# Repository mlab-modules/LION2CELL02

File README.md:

# LION2CELL02 - Dual-cell Li-Ion BMS with I2C interface and USB-C charging.

The LION2CELL02 module is designed to manage the charging and protection of the 2-cell Li-Ion battery stack. It incorporates advanced safe and efficient battery management features, utilizing the BQ40Z50-R2 fuel gauge and BQ25792 battery charger ICs.

## Features

The LION2CELL02 module include USB-C connector for quick charge connection. This allows for easy integration with USB-C power sources.

### BQ40Z50-R2 - Fuel Gauge

- Utilizes Impedance Track™ technology for accurate charge measurement.
- High-side protection N-FETs control.
- Integrated cell balancing during charging or at rest.
- Programmable protection features (voltage, current, temperature, charge timeout).
- JEITA, enhanced charging, and adaptive charging algorithms.
- Supports TURBO Mode 2.0 and Battery Trip Point (BTP).
- LED display for battery status.
- SMBus v1.1 interface for communication with the charger and host systems.

### BQ25792 Battery Charger

- Supports USB BC 1.2 charging standard.
- High-efficiency buck-boost charging for Li-Ion batteries.
- Programmable input current, charge current, and charge voltage.
- Integrated power path management.
- Protection features including overvoltage, undervoltage, overcurrent, and thermal protection.
- Low quiescent current for extended battery life.

## Power Delivery

The module supports BC 1.2 for charging. For the full USB Power Delivery (PD) support, an external USB PD controller is required. The MLAB [USBPDSINK01](https://www.mlab.cz/module/USBPDSINK01/) module can be used to enable PD functionality.

## Usage Instructions

1. Equip the LION2CELL02 module with pair of the suitable 16850 Li-Ion batteries.
2. Connect a USB-C power source to the module. For standard charging, ensure the power source complies with BC 1.2.
3. For USB PD, connect the USBPDSINK01 module to enable PD negotiation and charging.
4. Monitor the LED indicators for battery and charging status.
5. Connect to an MCU and use I2C/smbus for advanced features. 

## Safety and Protection

- The module includes multiple layers of protection for voltage, current, and temperature to ensure safe operation.
- Integrated cell balancing ensures equal charging across all cells, preventing overcharge and extending battery life.

## Applications

- UPS/battery backup systems
- Stand-alone measurement devices
- Scientific equipment

## Additional Resources

For further information, refer to the datasheets:
- [BQ40Z50-R2 Datasheet](https://www.ti.com/product/BQ40Z50-R2)
- [BQ25792 Datasheet](https://www.ti.com/product/BQ25792)

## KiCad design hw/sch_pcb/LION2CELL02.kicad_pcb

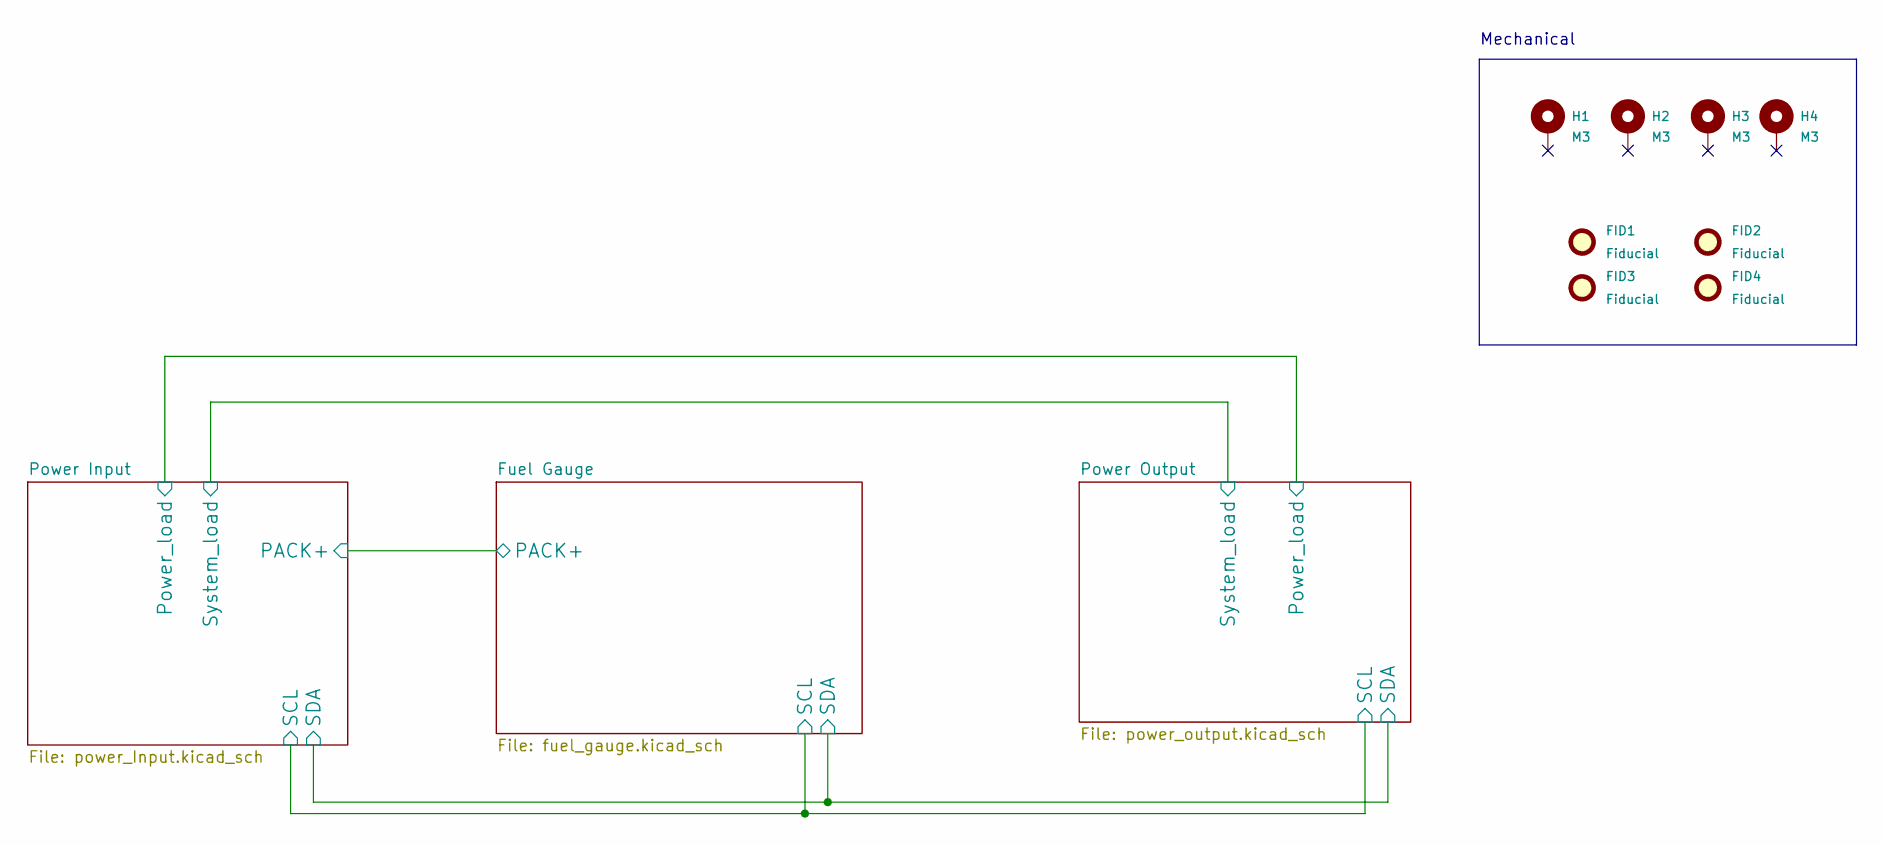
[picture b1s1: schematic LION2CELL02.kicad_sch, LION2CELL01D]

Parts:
FID1, FID2, FID3, FID4: Fiducial; Fiducial_1mm_Mask2mm
H1, H2, H3, H4: M3; MountingHole_3mm

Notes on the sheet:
Mechanical

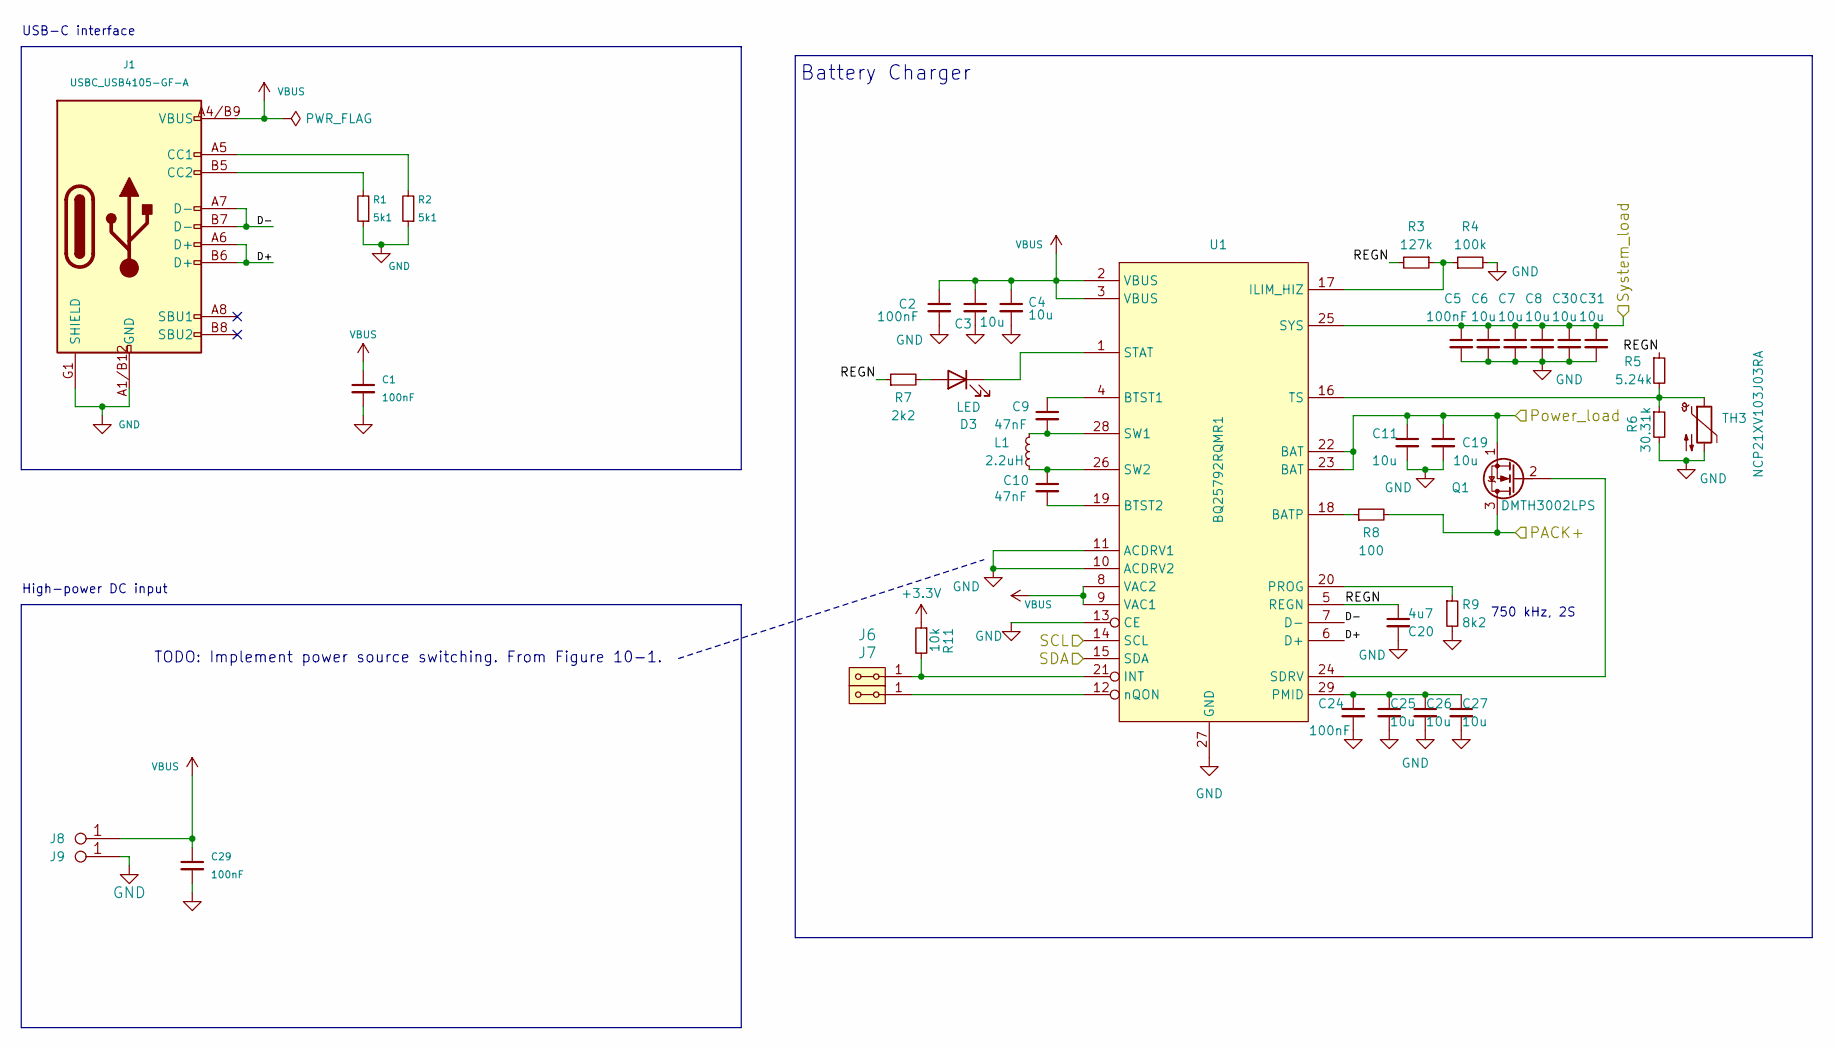
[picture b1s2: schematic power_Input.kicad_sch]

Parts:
C1, C2: 100nF; C_0805_2012Metric
C3, C4, C6, C7, C8, C11, C19, C25, C26, C27, C30, C31: 10u; C_0805_2012Metric
C5, C24: 100nF; C_0603_1608Metric
C9, C10: 47nF; C_0805_2012Metric
C20: 4u7; C_0805_2012Metric
C29: 100nF; C_0805_2012Metric; MPN C0805 1u
D3: LED; LED_1206
J1: USBC_USB4105-GF-A; USBC GCT_USB4105-GF-A; MPN USB4105-GF-A
J6, J7: HEADER_2x01_PARALLEL; Straight_2x01
J8, J9: CONN1_1; WAGO256
L1: 2.2uH; L_Vishay_IHLP-2020
Q1: DMTH3002LPS; D_POWERDI5060-8_6.0x5.1mm_P1.27mm
R1, R2: 5k1; R_0805_2012Metric
R3: 127k; R_0805_2012Metric
R4: 100k; R_0805_2012Metric
R5: 5.24k; R_0805_2012Metric
R6: 30.31k; R_0805_2012Metric
R7: 2k2; R_0805_2012Metric
R8: 100; R_0805_2012Metric
R9: 8k2; R_0805_2012Metric
R11: 10k; R_0805_2012Metric
TH3: NCP21XV103J03RA; R_0805_2012Metric
U1: BQ25792RQMR1; Texas_RQM0029A_VQFN-HR-28_4x4mm_P0.5mm

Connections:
+3.3V: R11.1; also elsewhere on the board
/Fuel Gauge/PACK+: Q1.3 (D), R8.2; also elsewhere on the board
/Fuel Gauge/SCL: U1.14 (SCL); also elsewhere on the board
/Fuel Gauge/SDA: U1.15 (SDA); also elsewhere on the board
/Power Input/D+: J1.A6 (D+), J1.B6 (D+), U1.6 (D+)
/Power Input/D-: J1.A7 (D-), J1.B7 (D-), U1.7 (D-)
/Power Input/Power_load: C11.1, C19.1, Q1.1 (S), U1.22 (BAT), U1.23 (BAT); also elsewhere on the board
/Power Input/REGN: C20.1, R3.2, R5.1, R7.1, U1.5 (REGN)
/Power Input/System_load: C5.1, C6.1, C7.1, C8.1, C30.1, C31.1, U1.25 (SYS); also elsewhere on the board
GND: C1.2, C2.2, C3.2, C4.2, C5.2, C6.2, C7.2, C8.2, C11.2, C19.2, C20.2, C24.2, C25.2, C26.2, C27.2, C29.2, C30.2, C31.2, J1.A1/B12 (GND), J1.B1/A12 (GND), J1.G1 (SHIELD), J1.G2 (SHIELD), J1.G3 (SHIELD), J1.G4 (SHIELD), J9.1, R1.1, R2.1, R4.2, R6.2, R9.2, TH3.2, U1.10 (ACDRV2), U1.11 (ACDRV1), U1.13 (CE), U1.27 (GND); also elsewhere on the board
unnamed: D3.2 (A), R7.2
unnamed: D3.1 (K), U1.1 (STAT)
unnamed: J1.A5 (CC1), R2.2
unnamed: J1.B5 (CC2), R1.2
unnamed: Q1.2 (G), U1.24 (SDRV)
unnamed: R8.1, U1.18 (BATP)
unnamed: C9.1, U1.4 (BTST1)
unnamed: C10.2, U1.19 (BTST2)
unnamed: R3.1, R4.1, U1.17 (ILIM_HIZ)
unnamed: J6.1, J6.2, R11.2, U1.21 (INT)
unnamed: C24.1, C25.1, C26.1, C27.1, U1.29 (PMID)
unnamed: R9.1, U1.20 (PROG)
unnamed: C9.2, L1.2, U1.28 (SW1)
unnamed: C10.1, L1.1, U1.26 (SW2)
unnamed: R5.2, R6.1, TH3.1, U1.16 (TS)
unnamed: J7.1, J7.2, U1.12 (nQON)
VBUS: C1.1, C2.1, C3.1, C4.1, C29.1, J1.A4/B9 (VBUS), J1.B4/A9 (VBUS), J8.1, U1.2 (VBUS), U1.3 (VBUS), U1.8 (VAC2), U1.9 (VAC1)

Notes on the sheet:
Battery Charger
High-power DC input
USB-C interface
750 kHz, 2S
TODO: Implement power source switching. From Figure 10-1.

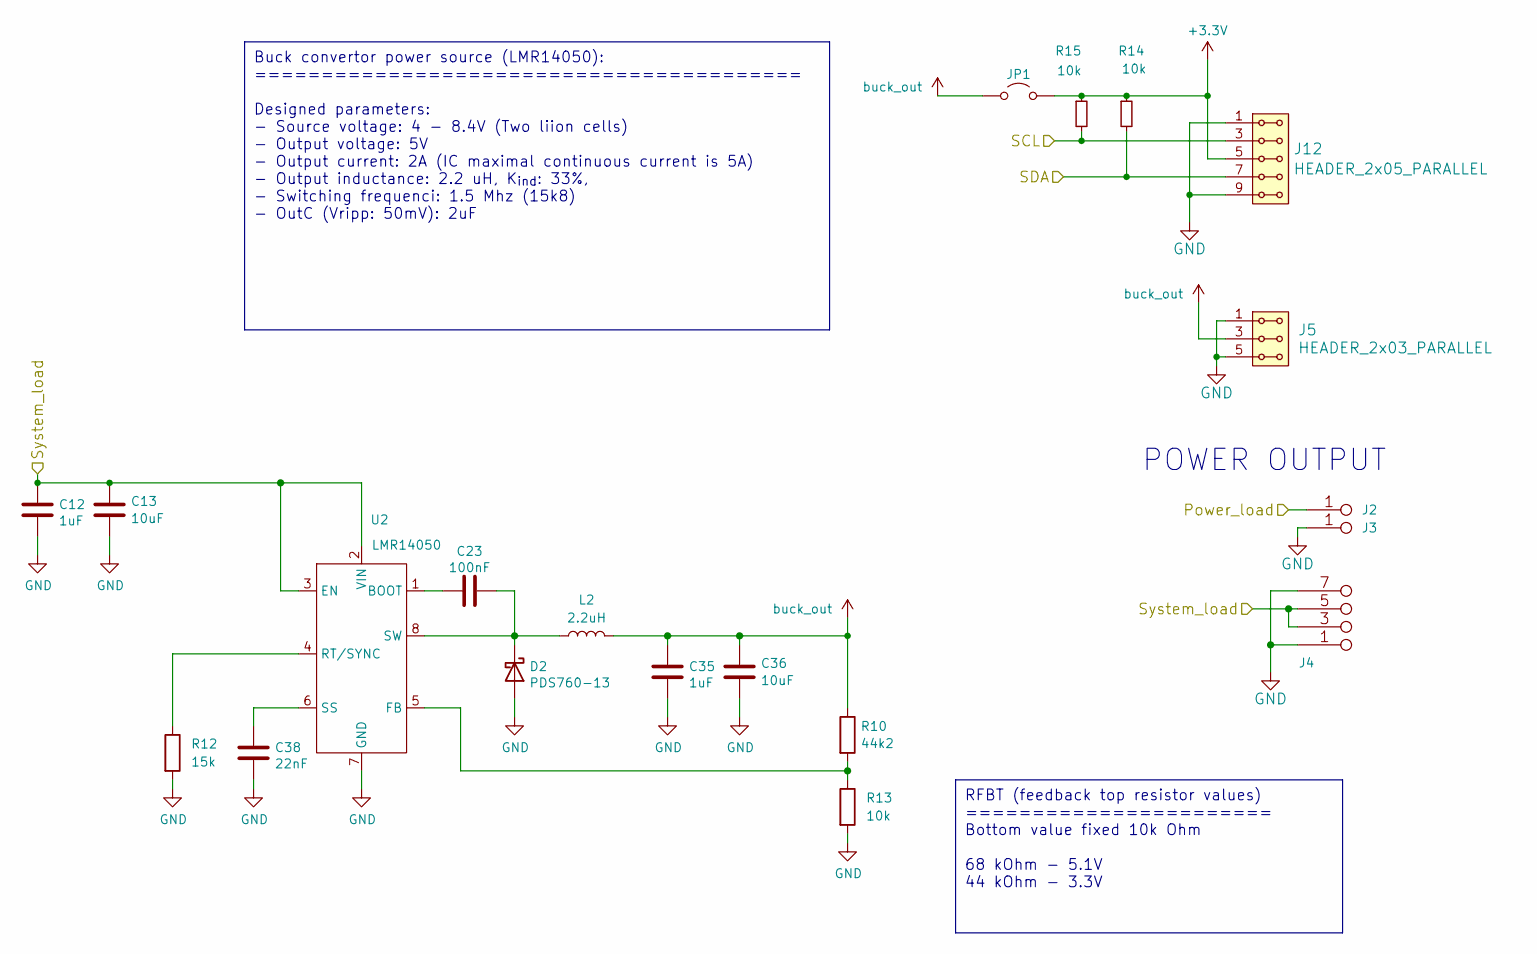
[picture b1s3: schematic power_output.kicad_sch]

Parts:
C12, C35: 1uF; C_0805_2012Metric
C13, C36: 10uF; C_0805_2012Metric
C23: 100nF; C_0805_2012Metric
C38: 22nF; C_0805_2012Metric
D2: PDS760-13; D_PowerDI-5
J2, J3: CONN1_1; WAGO256
J4: JUMP_4X2; Straight_2x04
J5: HEADER_2x03_PARALLEL; Straight_2x03
J12: HEADER_2x05_PARALLEL; Straight_2x05
JP1: Jumper_2_Open; Straight_2x01
L2: 2.2uH; L_Vishay_IHLP-2020
R10: 44k2; R_0805_2012Metric
R12: 15k; R_0805_2012Metric
R13, R14, R15: 10k; R_0805_2012Metric
U2: LMR14050; SOIC-8-1EP_3.9x4.9mm_P1.27mm_EP2.41x3.3mm_ThermalVias

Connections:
+3.3V: J12.5, J12.6, JP1.2 (B), R14.1, R15.1; also elsewhere on the board
/Fuel Gauge/SCL: J12.3, J12.4, R15.2; also elsewhere on the board
/Fuel Gauge/SDA: J12.7, J12.8, R14.2; also elsewhere on the board
/Power Input/Power_load: J2.1; also elsewhere on the board
/Power Input/System_load: C12.1, C13.1, J4.3 (4), J4.4, J4.5, J4.6 (5), U2.2 (VIN), U2.3 (EN); also elsewhere on the board
GND: C12.2, C13.2, C35.2, C36.2, C38.2, D2.2 (A), J3.1, J4.1 (2), J4.2, J4.7 (8), J4.8, J5.1, J5.2, J5.5, J5.6, J12.1, J12.2, J12.9, J12.10, R12.2, R13.2, U2.7 (GND), U2.9 (GND); also elsewhere on the board
unnamed: C23.2, D2.1 (K), L2.1, U2.8 (SW)
unnamed: C23.1, U2.1 (BOOT)
unnamed: R10.2, R13.1, U2.5 (FB)
unnamed: R12.1, U2.4 (RT/SYNC)
unnamed: C38.1, U2.6 (SS)
buck_out: C35.1, C36.1, J5.3, J5.4, JP1.1 (A), L2.2, R10.1

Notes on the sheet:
Buck convertor power source (LMR14050): ========================================= Designed parameters: - Source voltage: 4 - 8.4V (Two liion cells) - Output voltage: 5V - Output current: 2A (IC maximal continuous current is 5A) - Output inductance: 2.2 uH, K_{ind}: 33%, - Switching frequenci: 1.5 M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
RFBT (feedback top resistor values) ======================= Bottom value fixed 10k Ohm 68 kOhm - 5.1V 44 kOhm - 3.3V
POWER OUTPUT

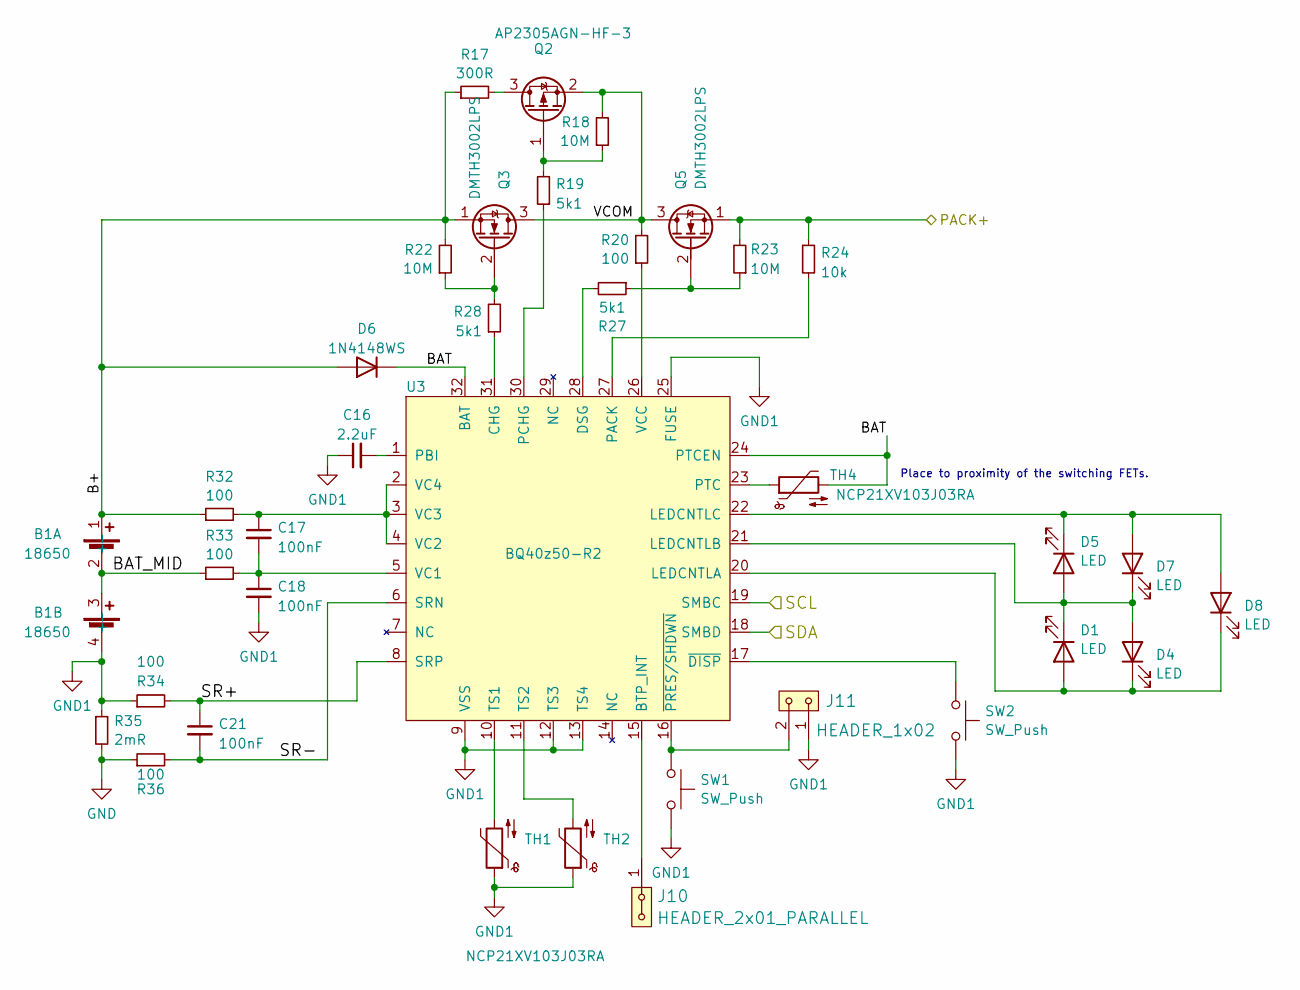
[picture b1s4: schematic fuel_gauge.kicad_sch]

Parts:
B1: 18650; BAT_BK-18650-PC4_no_screws
C16: 2.2uF; C_0805_2012Metric
C17, C18, C21: 100nF; C_0805_2012Metric; LCSC C1525
D1, D4, D5, D7, D8: LED; LED_1206
D6: 1N4148WS; D_0805_2012Metric
J10: HEADER_2x01_PARALLEL; Straight_2x01
J11: HEADER_1x02; Straight_2x01
Q2: AP2305AGN-HF-3; SOT-23
Q3, Q5: DMTH3002LPS; D_POWERDI5060-8_6.0x5.1mm_P1.27mm; Manufacturer_Part_Number DMT31M7LPS-13
R17: 300R; R_1206_3216Metric
R18, R22, R23: 10M; R_0805_2012Metric; LCSC C26082
R19, R27, R28: 5k1; R_0805_2012Metric; LCSC C25905
R20, R32, R33: 100; R_0805_2012Metric; LCSC C17408
R24: 10k; R_0805_2012Metric; LCSC C25744
R34, R36: 100; R_0805_2012Metric; LCSC C25076
R35: 2mR; R_2512_6332Metric
SW1, SW2: SW_Push; SW_PUSH_SMALL
TH1, TH2: NCP21XV103J03RA; R_0805_2012Metric; LCSC C279801
TH4: NCP21XV103J03RA; R_0805_2012Metric
U3: BQ40z50-R2; Texas_RSM0032A_VQFN-32-4.1x4.1-EP-1.4; LCSC C179743

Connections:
/Fuel Gauge/B+: B1.1 (+), D6.2 (A), Q3.1 (S), R17.1, R22.2, R32.1
/Fuel Gauge/BAT: D6.1 (K), TH4.2, U3.24 (PTCEN), U3.32 (BAT)
/Fuel Gauge/BAT_MID: B1.2 (-), B1.3 (+), R33.1
/Fuel Gauge/PACK+: Q5.1 (S), R23.2, R24.1; also elsewhere on the board
/Fuel Gauge/SCL: U3.19 (SMBC); also elsewhere on the board
/Fuel Gauge/SDA: U3.18 (SMBD); also elsewhere on the board
/Fuel Gauge/SR+: C21.1, R34.2, U3.8 (SRP)
/Fuel Gauge/SR-: C21.2, R36.2, U3.6 (SRN)
/Fuel Gauge/VCOM: Q2.2 (S), Q3.3 (D), Q5.3 (D), R18.2, R20.2
GND: R35.2, R36.1; also elsewhere on the board
GND1: B1.4 (-), C16.1, C18.2, J11.1, R34.1, R35.1, SW1.2, SW2.2, TH1.1, TH2.1, U3.9 (VSS), U3.12 (TS3), U3.13 (TS4), U3.25 (FUSE), U3.33 (PWRPD)
unnamed: D1.2 (A), D4.1 (K), D8.1 (K), U3.20 (LEDCNTLA)
unnamed: D1.1 (K), D4.2 (A), D5.2 (A), D7.1 (K), U3.21 (LEDCNTLB)
unnamed: D5.1 (K), D7.2 (A), D8.2 (A), U3.22 (LEDCNTLC)
unnamed: Q2.3 (D), R17.2
unnamed: Q2.1 (G), R18.1, R19.2
unnamed: Q3.2 (G), R22.1, R28.2
unnamed: Q5.2 (G), R23.1, R27.1
unnamed: J10.1, J10.2, U3.15 (BTP_INT)
unnamed: R28.1, U3.31 (CHG)
unnamed: R27.2, U3.28 (DSG)
unnamed: R24.2, U3.27 (PACK)
unnamed: C16.2, U3.1 (PBI)
unnamed: R19.1, U3.30 (PCHG)
unnamed: TH4.1, U3.23 (PTC)
unnamed: TH1.2, U3.10 (TS1)
unnamed: TH2.2, U3.11 (TS2)
unnamed: C17.2, C18.1, R33.2, U3.5 (VC1)
unnamed: C17.1, R32.2, U3.2 (VC4), U3.3 (VC3), U3.4 (VC2)
unnamed: R20.1, U3.26 (VCC)
unnamed: SW2.1, U3.17 (~DISP)
unnamed: J11.2, SW1.1, U3.16 (~PRES/SHDWN)

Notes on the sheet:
Place to proximity of the switching FETs.

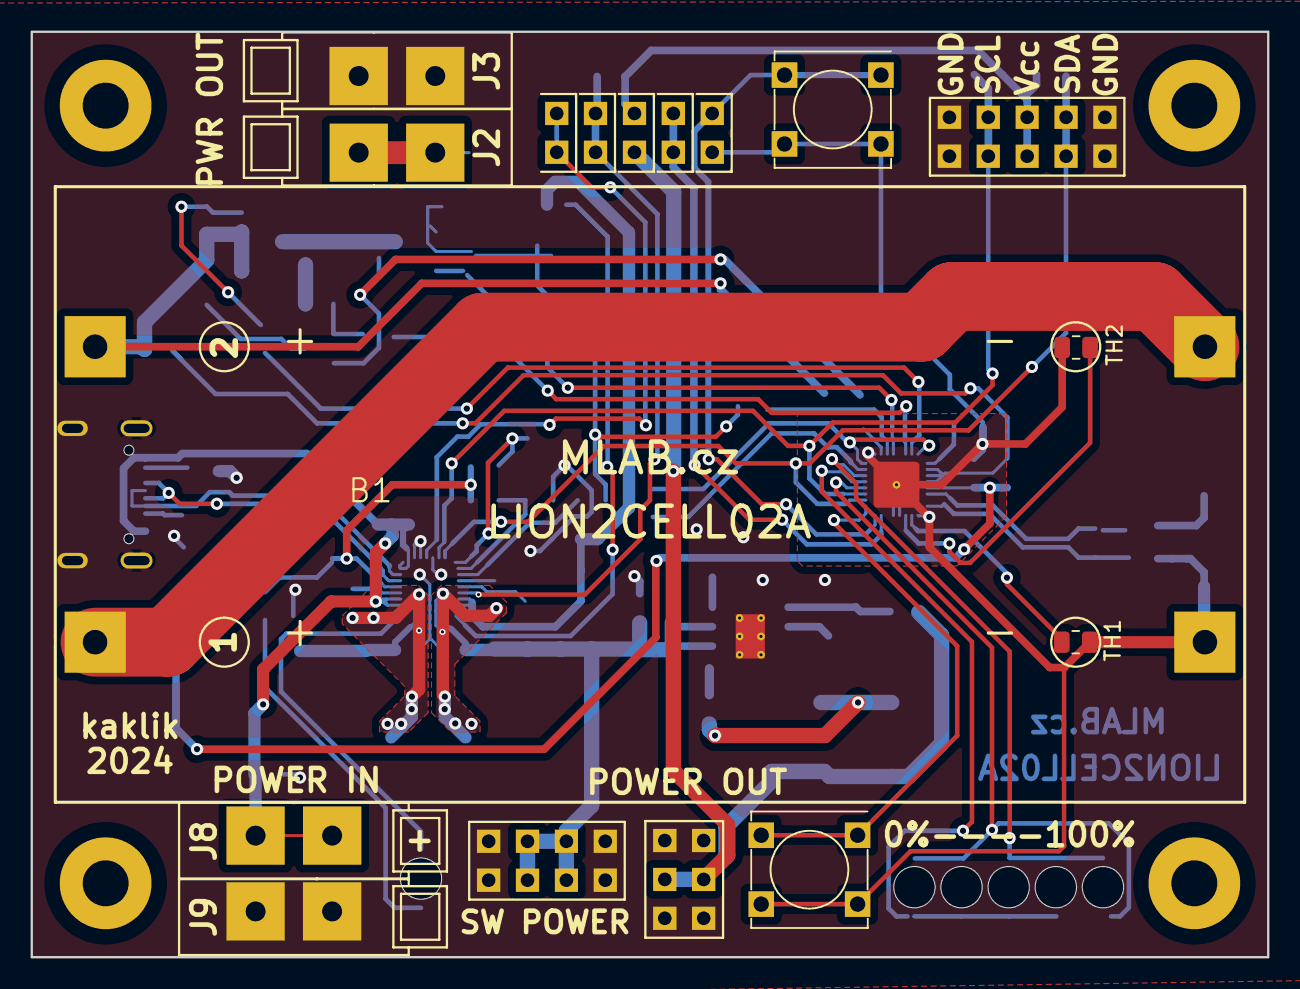
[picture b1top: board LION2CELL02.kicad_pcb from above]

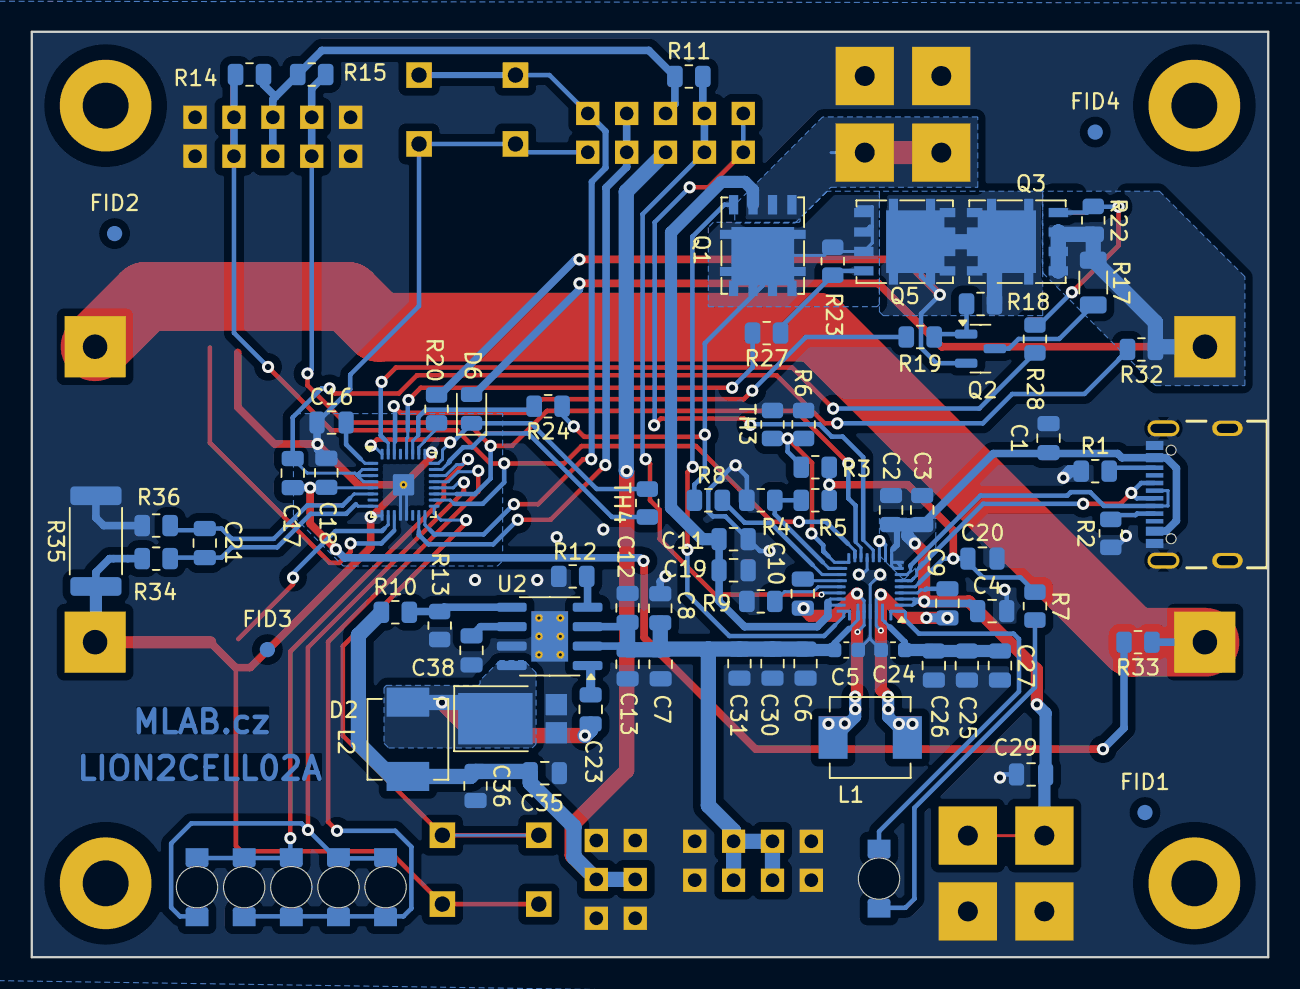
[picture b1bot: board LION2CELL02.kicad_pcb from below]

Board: 2 copper layers, 80.8 x 60.5 mm, 104 parts (83 on the bottom side), 61 nets.

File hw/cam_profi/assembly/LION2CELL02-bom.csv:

Component,Description,Part,References,Value,Footprint,Quantity Per PCB,Datasheet,ust_id,lcsc,mfpn,mpn,manufacturer_part_number
1,,battery-2s,B1,18650,BAT_BK-18650-PC4_no_screws,1,,5c70984412875079b91f87e9,,,,
2,Unpolarized capacitor,C,C38,22nF,C_0805_2012Metric,1,~,5c70984712875079b91f8b4a,,,,
3,"Unpolarized capacitor, small symbol",C_Small,C9C10,47nF,C_0805_2012Metric,2,~,65482046462c6d9e72056b98,,,,
4,"Unpolarized capacitor, small symbol",C_Small,C1C2C17C18C21C23C29,100nF,C_0805_2012Metric,7,~,5c70984712875079b91f8b4c,C1525,C0805 1u,C0805 1u,
5,"Unpolarized capacitor, small symbol",C_Small,C5C24,100nF,C_0603_1608Metric,2,~,5c70984812875079b91f8bf2,,,,
6,Unpolarized capacitor,C,C12C35,1uF,C_0805_2012Metric,2,~,5c70984712875079b91f8b6f,,,,
7,"Unpolarized capacitor, small symbol",C_Small,C16,2.2uF,C_0805_2012Metric,1,~,5c70984712875079b91f8b51,,,,
8,"Unpolarized capacitor, small symbol",C_Small,C20,4u7,C_0805_2012Metric,1,~,5e3ff8fc1287502a33bad7a3,,,,
9,"Unpolarized capacitor, small symbol",C_Small,C3C4C6C7C8C11C13C19C25C26C27C30C31C36,10u,C_0805_2012Metric,14,~,5c70984712875079b91f8b53 607c1245128750769ee58ca7,,,,
10,"75V 0.15A Fast switching Diode, SOD-323",1N4148WS,D6,1N4148WS,D_0805_2012Metric,1,https://www.vishay.com/docs/85751/1n4148ws.pdf,5c70984512875079b91f88c5,,,,
11,Light emitting diode,LED,D1D3D4D5D7D8,LED,LED_1206,6,~,5c70984412875079b91f8892,,,,
12,Schottky diode,D_Schottky,D2,PDS760-13,D_PowerDI-5,1,~,6087aaaf128750769ee58fb7,,,,
13,,CONN1_1,J2J3J8J9,CONN1_1,WAGO256,4,,,,,,
14,1x02 2.54 mm pitch header,HEADER_1x02,J11,HEADER_1x02,Straight_2x01,1,,,,,,
15,"2x01 2.54 mm pitch header, 2 pins next to each other are connected",HEADER_2x01_PARALLEL,J6J7J10,HEADER_2x01_PARALLEL,Straight_2x01,3,,,,,,
16,"2x03 2.54 mm pitch header, 2 pins next to each other are connected",HEADER_2x03_PARALLEL,J5,HEADER_2x03_PARALLEL,Straight_2x03,1,,,,,,
17,"2x05 2.54 mm pitch header, 2 pins next to each other are connected",HEADER_2x05_PARALLEL,J12,HEADER_2x05_PARALLEL,Straight_2x05,1,,,,,,
18,,JUMP_4X2,J4,JUMP_4X2,Straight_2x04,1,,,,,,
19,USB 2.0-only Type-C Receptacle connector,USBC_USB4105-GF-A,J1,USBC_USB4105-GF-A,USBC GCT_USB4105-GF-A,1,,5fa0f94612875025b397795e,,USB4105-GF-A,USB4105-GF-A,
20,"Jumper, 2-pole, open",Jumper_2_Open,JP1,Jumper_2_Open,Straight_2x01,1,~,,,,,
21,"Inductor, small symbol",L_Small,L1L2,2.2uH,L_Vishay_IHLP-2020,2,https://www.vishay.com/docs/34563/ihlp-2020cz-8a.pdf,669e8efe6fdfe6f54e2eb7e6,,,,
22,"-4.0A Id, -30V Vds, P-Channel MOSFET, SOT-23",AO3401A,Q2,AP2305AGN-HF-3,SOT-23,1,https://www.tme.eu/Document/fc64476bcfec1f3af35a324c08c5f351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,5c70984712875079b91f8af1,,,,
23,"N-MOSFET transistor, source/gate/drain",Q_NMOS_SGD,Q1Q3Q5,DMTH3002LPS,D_POWERDI5060-8_6.0x5.1mm_P1.27mm,3,https://eu.mouser.com/datasheet/2/115/DIOD_S_A0003132884_1-2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,669990696fdfe6f54e2eb28a,,,,DMT31M7LPS-13
24,"Resistor, small symbol",R_Small,R35,2mR,R_2512_6332Metric,1,https://www.tme.eu/Document/9eb17c5caf6d68fb7c80b751e0adae3a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,669ba41c6fdfe6f54e2eb51d,,,,
25,"Resistor, small symbol",R_Small,R8R20R32R33R34R36,100,R_0805_2012Metric,6,~,5c70984512875079b91f8977,C17408 C25076,,,
26,"Resistor, small symbol",R_Small,R17,300R,R_1206_3216Metric,1,~,5c70984712875079b91f8ab8,,,,
27,"Resistor, small symbol",R_Small,R7,2k2,R_0805_2012Metric,1,~,5c70984612875079b91f8990,,,,
28,"Resistor, small symbol",R_Small,R1R2R19R27R28,5k1,R_0805_2012Metric,5,~,5fa0fc3e12875025b3977997,C25905,,,
29,"Resistor, small symbol",R_Small,R5,5.24k,R_0805_2012Metric,1,~,66a159d36fdfe6f54e2ebef5,,,,
30,"Resistor, small symbol",R_Small,R9,8k2,R_0805_2012Metric,1,~,5c70984612875079b91f899c,,,,
31,"Resistor, small symbol",R_Small,R11R13R14R15R24,10k,R_0805_2012Metric,5,~,5c70984612875079b91f899f,C25744,,,
32,Resistor,R,R12,15k,R_0805_2012Metric,1,~,5c70984712875079b91f8b6a,,,,
33,"Resistor, small symbol",R_Small,R6,30.31k,R_0805_2012Metric,1,~,66a15a4a6fdfe6f54e2ebf1b,,,,
34,Resistor,R,R10,44k2,R_0805_2012Metric,1,~,669ebdcc6fdfe6f54e2eb869,,,,
35,"Resistor, small symbol",R_Small,R4,100k,R_0805_2012Metric,1,~,639ed3d540d28a66c9e88a9e,,,,
36,"Resistor, small symbol",R_Small,R3,127k,R_0805_2012Metric,1,~,66a1559d6fdfe6f54e2ebeaa,,,,
37,"Resistor, small symbol",R_Small,R18R22R23,10M,R_0805_2012Metric,3,~,5c70984712875079b91f8aae,C26082,,,
38,"Push button switch, generic, two pins",SW_Push,SW1SW2,SW_Push,SW_PUSH_SMALL,2,~,5c70984712875079b91f8ad2,,,,
39,"Temperature dependent resistor, negative temperature coefficient",Thermistor_NTC,TH1TH2TH3TH4,NCP21XV103J03RA,R_0805_2012Metric,4,~,5c70984712875079b91f8ac5,C279801,,,
40,,BQ25792RQMR,U1,BQ25792RQMR1,Texas_RQM0029A_VQFN-HR-28_4x4mm_P0.5mm,1,https://www.ti.com/lit/ds/symlink/bq25792.pdf,66a15cdb6fdfe6f54e2ebf66,,,,
41,,BQ40z50-R2,U3,BQ40z50-R2,Texas_RSM0032A_VQFN-32-4.1x4.1-EP-1.4,1,http://www.ti.com/lit/ds/symlink/bq40z50-r2.pdf,66a15dd06fdfe6f54e2ebf93,C179743,,,
42,,LMR14050,U2,LMR14050,SOIC-8-1EP_3.9x4.9mm_P1.27mm_EP2.41x3.3mm_ThermalVias,1,https://www.ti.com/lit/ds/symlink/lmr14050.pdf,6087b6ba128750769ee59110,,,,

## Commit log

2024-07-17 Update metadata files
2024-07-17 Initial work on the BMS module.
2024-07-18 Update workflow files
2024-07-18 Initial work on battery charging.
2024-07-19 work of the schematics of charger completed.
2024-07-19 Fuel gauge schematics work done.
2024-07-19 Schematics work. PCB layout initial schematics import.
2024-07-20 Updated workflows.
2024-07-20 Improve documentation.
2024-07-20 Update actions products
2024-07-20 Layout WiP.
2024-07-21 Partially routed PCB.
2024-07-21 Routed few aditional nets Battery mid-point zone connection changed to a track with special net class.
2024-07-21 PCB routing WiP.
2024-07-21 Routed another tracks.
2024-07-21 The first completely routed nets.
2024-07-21 Adding output voltage switching regulator.
2024-07-22 Minimizing output regulator components count.
2024-07-22 update power-output schematic
2024-07-22 Reduce complexity of layout.
2024-07-22 Cleanup routing. Adding 5V output connector.
2024-07-22 Syncing board with schematics. Roughly placing the switching regulator.
2024-07-22 Routed switching regulator Starting of layout cleanup. Uniforming of charger and switching regulator inductors.
2024-07-23 Uniforming track width Cleanup layout. Fix high-current paths Create copper-pours to high-current areas.
2024-07-23 Correct positioning of FIDUs Fix silkscreen texts.
2024-07-24 USB data lines layout improvement. Zones definitions for improving noise imunity.
2024-07-24 Resolve DRC issues. Update footprints. Improve silkscreen.
2024-07-24 Update USTids.
2024-07-24 Fix missing assigments.
2024-07-24 Fix whitespaces around USTids.
2024-07-26 Fix fab layer.
2024-08-08 Fix components identification.
2024-08-08 Update PCB from schematics.
2024-09-18 Adding initial configuration for Murata cells.
2024-11-08 Move reference to avoid collision.
2024-11-09 Update documentation. Add Tindie listing.
2025-02-25 Update metadata.yaml
    Update module status.
2025-02-25 Update metadata.yaml
    Add link to tindie store.
